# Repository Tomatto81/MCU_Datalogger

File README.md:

## ⚙️ MCU Data Logger – PCB Design with KiCad  

### 📋 Project Overview

**MCU Data Logger** is a custom PCB that records sensor or system data over time.

It's built around an **ATmega328P‑AU** microcontroller and uses an **EEPROM** (24LC1025) to keep the data even after power is removed. A **DS1337 real‑time clock** timestamps every entry, so you know exactly when something happened.

The board talks to the outside world through **UART, SPI, and I2C** – you can connect it to sensors, displays, or another microcontroller. I also brought out a few spare GPIOs in case you want to add more features later.

The whole design was done in **KiCad** using a **4‑layer stackup** (signal – GND – VCC – signal) to keep noise low and routing tidy.

### 🔧 Key Features

- **4-layer PCB** – Designed and routed in KiCad.
- **ATmega328P-AU** – Main microcontroller for processing and control.
- **💾 24LC1025 EEPROM** – Non‑volatile storage for logged data.
- **⏱️ DS1337 RTC** – Real‑time clock for accurate timestamps.
- **🔌 UART, SPI, I2C** – Multiple communication interfaces.
- **📈 Spare GPIOs** – Brought out for future expansion.

---

## 🔄 Project Flow  

1️⃣ **Microcontroller (ATmega328P-AU)**  
   - Handles all system operations and manages communication.  
   - Reads and writes data to EEPROM for storage.  
   
2️⃣ **RTC Module (DS1337)**  
   - Provides accurate timestamps for logged data.  
   - Communicates via I2C with the MCU.  
   
3️⃣ **EEPROM Storage (24LC1025)**  
   - Stores logged data persistently.  
   - Connected over I2C for data transfer.  

4️⃣ **Communication Interfaces**  
   - **UART**: Serial communication for debugging/logging.  
   - **SPI & I2C**: Expandability for additional peripherals.  

5️⃣ **Power Management & PCB Layout**  
   - Designed for stable operation with proper power routing.  
   - Optimized signal paths to reduce interference and improve reliability.  

--- 

## 🖼️ PCB Design & Visualizations

### 1️⃣ Top Copper Layer

### 2️⃣ Bottom Copper Layer

### 3️⃣ MCU Datalogger Schematic

### 4️⃣ Connectors Schematic

### 5️⃣ 3D Model (Top & Bottom)

---

## 📥 Download & Build
The complete project files, including KiCad PCB designs and schematics, are available for download from my **GitHub repository**.

---

## 💬 Feedback & Suggestions
Please feel free to open an **issue** or leave a **comment**.

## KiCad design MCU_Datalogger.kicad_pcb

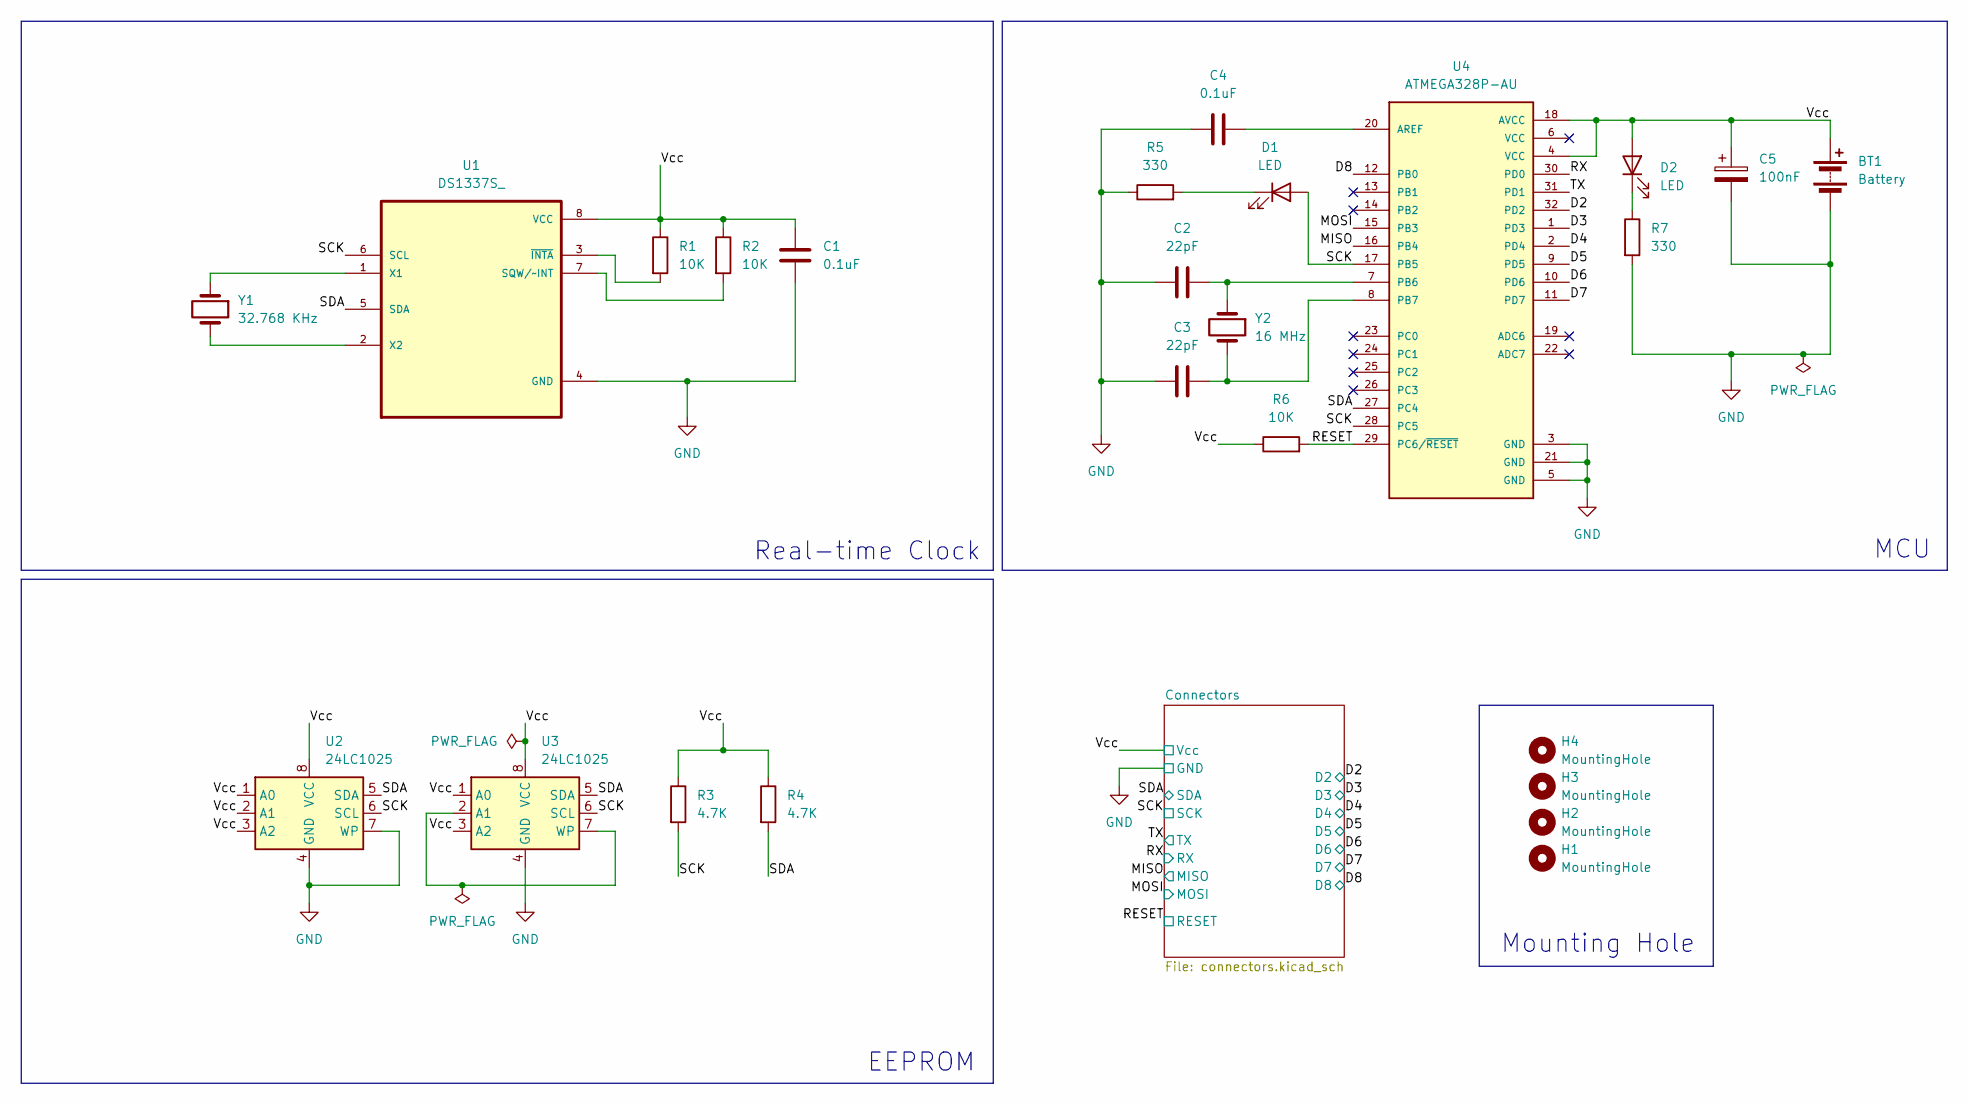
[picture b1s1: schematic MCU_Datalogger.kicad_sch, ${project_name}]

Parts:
BT1: Battery; PinHeader_1x02_P2.54mm_Vertical
C1, C4: 0.1uF; C_0805_2012Metric
C2, C3: 22pF; C_0805_2012Metric
C5: 100nF; C_0805_2012Metric
D1, D2: LED; LED_0805_2012Metric
H1, H2, H3, H4: MountingHole; MountingHole_2.1mm
R1, R2, R6: 10K; R_0805_2012Metric
R3, R4: 4.7K; R_0805_2012Metric
R5, R7: 330; R_0805_2012Metric
U1: DS1337S_; SOIC127P600X175-8N
U2, U3: 24LC1025; SOIC-8_5.3x5.3mm_P1.27mm
U4: ATMEGA328P-AU; QFP80P900X900X120-32N; PARTREV 8271A
Y1: 32.768 KHz; Crystal_SMD_5032-2Pin_5.0x3.2mm_HandSoldering
Y2: 16 MHz; Crystal_SMD_5032-2Pin_5.0x3.2mm_HandSoldering

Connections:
/D2: U4.32 (PD2); also elsewhere on the board
/D3: U4.1 (PD3); also elsewhere on the board
/D4: U4.2 (PD4); also elsewhere on the board
/D5: U4.9 (PD5); also elsewhere on the board
/D6: U4.10 (PD6); also elsewhere on the board
/D7: U4.11 (PD7); also elsewhere on the board
/D8: U4.12 (PB0); also elsewhere on the board
/MISO: U4.16 (PB4); also elsewhere on the board
/MOSI: U4.15 (PB3); also elsewhere on the board
/RESET: R6.2, U4.29 (PC6/~RESET); also elsewhere on the board
/RX: U4.30 (PD0); also elsewhere on the board
/SCK: D1.2 (A), R3.2, U1.6 (SCL), U2.6 (SCL), U3.6 (SCL), U4.17 (PB5), U4.28 (PC5); also elsewhere on the board
/SDA: R4.2, U1.5 (SDA), U2.5 (SDA), U3.5 (SDA), U4.27 (PC4); also elsewhere on the board
/TX: U4.31 (PD1); also elsewhere on the board
/Vcc: BT1.1 (+), C1.1, C5.1, D2.2 (A), R1.1, R2.1, R3.1, R4.1, R6.1, U1.8 (VCC), U2.1 (A0), U2.2 (A1), U2.3 (A2), U2.8 (VCC), U3.1 (A0), U3.3 (A2), U3.8 (VCC), U4.4 (VCC), U4.18 (AVCC); also elsewhere on the board
GND: BT1.2 (-), C1.2, C2.2, C3.2, C4.1, C5.2, R5.1, R7.2, U1.4 (GND), U2.4 (GND), U2.7 (WP), U3.4 (GND), U4.3 (GND), U4.5 (GND), U4.21 (GND); also elsewhere on the board
unnamed: D1.1 (K), R5.2
unnamed: D2.1 (K), R7.1
unnamed: R2.2, U1.7 (SQW/~INT)
unnamed: U1.1 (X1), Y1.1
unnamed: U1.2 (X2), Y1.2
unnamed: R1.2, U1.3 (~INTA)
unnamed: U3.2 (A1), U3.7 (WP)
unnamed: C4.2, U4.20 (AREF)
unnamed: C2.1, U4.7 (PB6), Y2.1
unnamed: C3.1, U4.8 (PB7), Y2.2

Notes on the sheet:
EEPROM
Real-time Clock
Mounting Hole
MCU

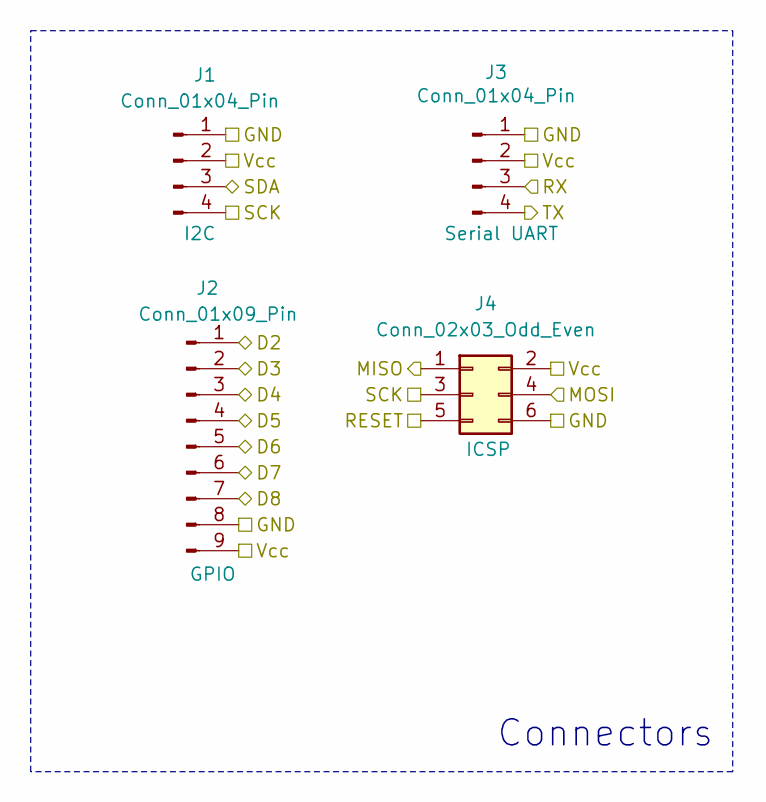
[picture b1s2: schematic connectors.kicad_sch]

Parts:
J1, J3: Conn_01x04_Pin; PinHeader_1x04_P2.54mm_Vertical
J2: Conn_01x09_Pin; PinHeader_1x09_P2.54mm_Vertical
J4: Conn_02x03_Odd_Even; PinHeader_2x03_P2.54mm_Vertical

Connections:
/D2: J2.1; also elsewhere on the board
/D3: J2.2; also elsewhere on the board
/D4: J2.3; also elsewhere on the board
/D5: J2.4; also elsewhere on the board
/D6: J2.5; also elsewhere on the board
/D7: J2.6; also elsewhere on the board
/D8: J2.7; also elsewhere on the board
/MISO: J4.1; also elsewhere on the board
/MOSI: J4.4; also elsewhere on the board
/RESET: J4.5; also elsewhere on the board
/RX: J3.3; also elsewhere on the board
/SCK: J1.4, J4.3; also elsewhere on the board
/SDA: J1.3; also elsewhere on the board
/TX: J3.4; also elsewhere on the board
/Vcc: J1.2, J2.9, J3.2, J4.2; also elsewhere on the board
GND: J1.1, J2.8, J3.1, J4.6; also elsewhere on the board

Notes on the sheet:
Connectors

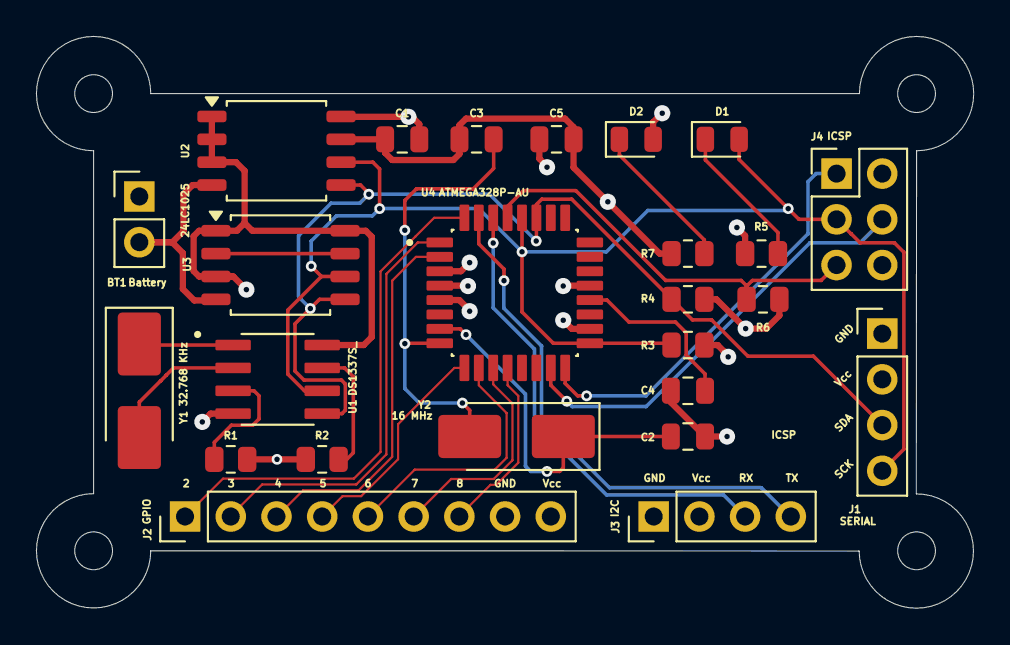
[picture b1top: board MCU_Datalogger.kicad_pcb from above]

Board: 4 copper layers, 52.1 x 31.8 mm, 29 parts (0 on the bottom side), 26 nets.

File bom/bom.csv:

"","Sourced","Placed","References","Value","Footprint","Quantity"
1,"","","C1, C4, C5","100nF","C_0805_2012Metric",3
2,"","","C2, C3","22pF","C_0805_2012Metric",2
3,"","","R1, R2, R6","10K","R_0805_2012Metric",3
4,"","","R3, R4","4.7K","R_0805_2012Metric",2
5,"","","R5, R7",330,"R_0805_2012Metric",2
6,"","","D1, D2","LED","LED_0805_2012Metric",2
7,"","","U2, U3","24LC1025","SOIC-8_5.3x5.3mm_P1.27mm",2
8,"","","U1","DS1337S_","SOIC127P600X175-8N",1
9,"","","U4","ATMEGA328P-AU","QFP80P900X900X120-32N",1
10,"","","Y1","32.768 KHz","Crystal_SMD_5032-2Pin_5.0x3.2mm_HandSoldering",1
11,"","","Y2","16 MHz","Crystal_SMD_5032-2Pin_5.0x3.2mm_HandSoldering",1
12,"","","BT1","Battery","PinHeader_1x02_P2.54mm_Vertical",1
13,"","","J1, J3","Conn_01x04_Pin","PinHeader_1x04_P2.54mm_Vertical",2
14,"","","J2","Conn_01x09_Pin","PinHeader_1x09_P2.54mm_Vertical",1
15,"","","J4","Conn_02x03_Odd_Even","PinHeader_2x03_P2.54mm_Vertical",1

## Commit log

2026-04-26 First commit of new project.
2026-04-26 Setup of the schematic editor for the new project.
2026-05-04 Added required symbols to the schematic sheets.
2026-05-05 Completed wiring of main sheet.
2026-05-14 Update setup for schematic editor.
2026-05-14 Completed schematic editor
2026-05-14 Setup PCB Editor
2026-05-14 Completed placement of footprints
2026-05-14 Refined and completed outline
2026-05-16 Ready to manufacture version 1
2026-05-17 Completed 2-layer PCB Project
2026-05-17 Remove gerber folder
2026-05-17 Rename project folder to remove space
2026-05-17 Completed 4-layer PCB routing
2026-05-17 Completed 4-layer PCB
2026-05-17 Add gitattributes
2026-05-18 Small change to schematic
2026-05-18 Update schematic
2026-05-18 Optimize PCB routing
2026-05-18 Fix folder
2026-05-18 Remove backups
2026-05-18 Improve PCB design, add images folder, and bom folder
2026-05-18 Update gitattributes
2026-05-19 add bom.csv
2026-05-19 add readme.md
